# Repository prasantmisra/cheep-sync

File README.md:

CheepSync: A Time Synchronization Service for Resource Constrained Bluetooth LE Advertisers
--------------------------------------------------------------------------------------------

Bluetooth Low Enegy (BLE) is a subset of the Bluetooth v4:0 stack, and is designed for low-power applications interested in knowing the state of the physical world.
BLE has inherited several technical features from Classic Bluetooth that provide for robust, reliable connections. However, the most significant difference is its asymmetric design. While the standard
mode of operation is typically based on a master device connected to a number of slave devices, it offers a new feature in the form of an ‘advertisement’ (configurable through the broadcast/peripheral mode of BLE).
BLE provides a range of broadcast advertising modes, of which the most energy efficient is the non-connectable undirected advertising mode (ADV_NONCONN_IND): a transmit-only, broadcaster mode without any listen window.

CheepSync is an open source time synchronization service for BLE advertisers in ADV_NONCONN_IND mode.
Designed on top of the existing Bluetooth v4.0 standard, the CheepSync framework utilizes low-leveltimestamping and comprehensive error compensation mechanisms
for overcoming uncertainties in message transmission, clock drift and other system specific constraints. 

The current implementation of CheepSync is on custom designed nRF24Cheep beacon platforms (as broadcasters) and commercial off-the-shelf Android ported
smartphones (as passive listeners).

Configurations:
--------------------------------------------------------------------------------------------
Transmitter:

1. Go to URL http://www.kpitgnutools.com/index.php, and register. Upon successful registration, you will receive a username and password by email.
2. Using these credentials, download RL78 installer along with e2studio.
3. Import ? into the e2studio IDE.

Receiver:

1. Install the custom android ROM for the phone.

  We used KitKat on Nexus 5. There are two ways to do it:
  
  First:--------------
    Build the android phone according to the blog post (http://nosemaj.org/howto-build-android-kitkat-nexus-5)
    For incremental builds:
      source build/envsetup.sh
      lunch
      make updatepackage -j10
      make snod
      mmm /path/to/directory
      sudo chmod -R 755 
  
  Second:-------------
    Refer the cynogenmod website (http://www.cyanogenmod.org/)
  
2. Root the android phone
3. Install busybox installer for android
4. Start the transmitter
5. Run the android application
6. Observe the file /sdcard/log_after using adb shell and observing the contents.

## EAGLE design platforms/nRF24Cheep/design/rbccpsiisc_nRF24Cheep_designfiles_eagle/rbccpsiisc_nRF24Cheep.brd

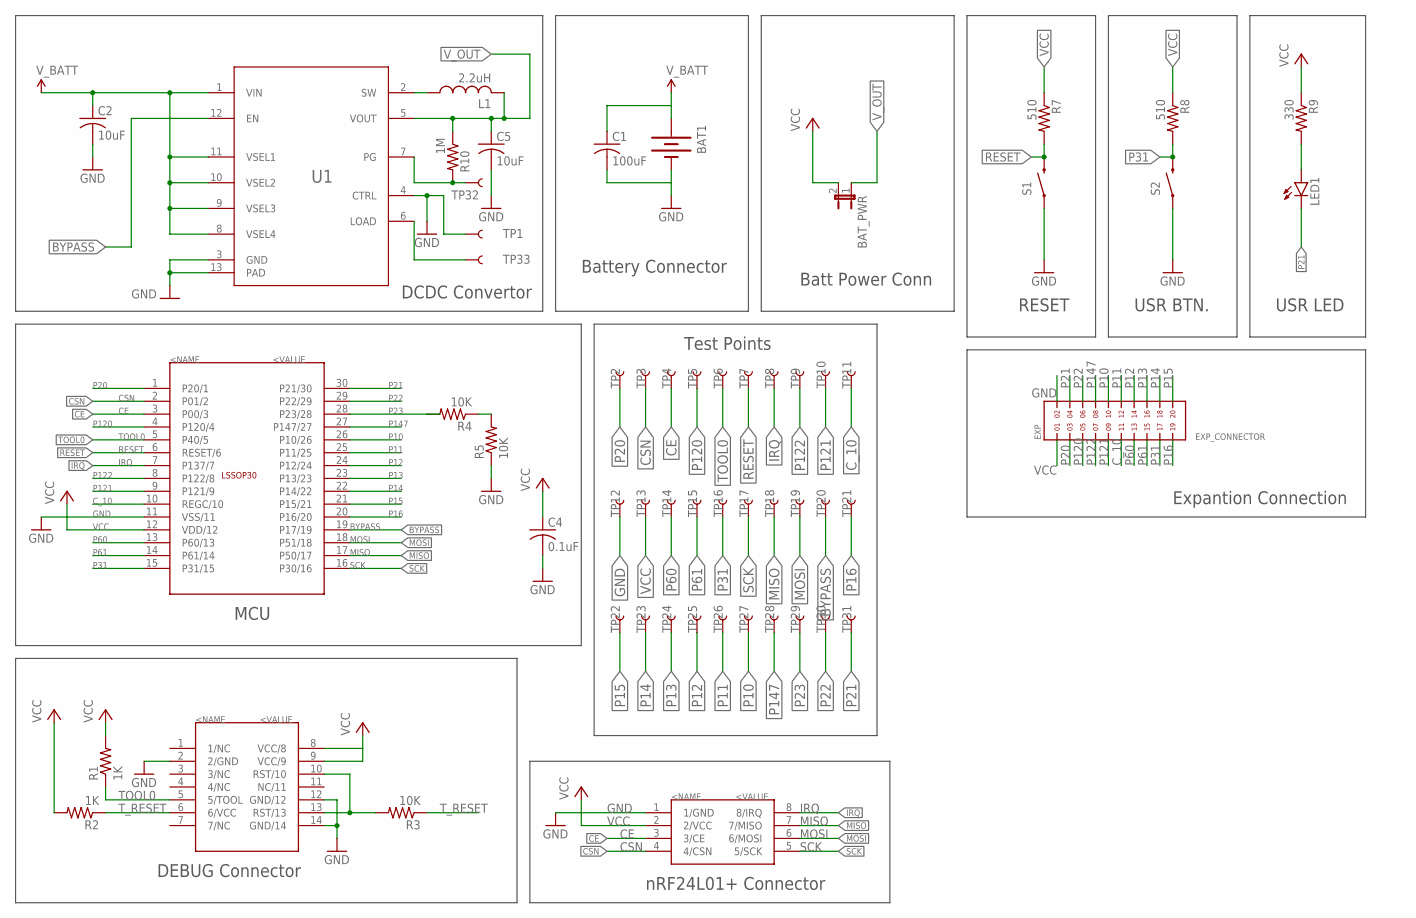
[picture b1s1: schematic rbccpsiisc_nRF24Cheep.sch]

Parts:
BAT1: BATTERY20SMD; BATTCON_20MM
BAT_PWR: JUMPER-2PTH; 1X02
C1: 100uF; C1206K
C2, C5: 10uF; C0603K
C4: 0.1uF; C0603K
EXP: EXP_CONNECTOR; 2X10
L1: 2.2uH; L2012C
LED1: LED0603; LED-0603
NRFSOCKET: BERG_NRF24_NRF24
R1, R2: 1K; R0603
R3, R4, R5: 10K; R0603
R7, R8: 510; R0603
R9: 330; R0603
R10: 1M; R0603
RENASENCE: SSOP30_SSOP30
S1, S2: SWITCH-MOMENTARY-2-SMD-1101NE; TACTILE-SWITCH-1101NE
TP1, TP2, TP3, TP4, TP5, TP6, TP7, TP8, TP9, TP10, TP11, TP12, TP13, TP14, TP15, TP16, TP17, TP18, TP19, TP20, TP21, TP22, TP23, TP24, TP25, TP26, TP27, TP28, TP29, TP30, TP31, TP32, TP33: TEST-POINT3X4; PAD.03X.04
U1: TPS62740DSST; DSS0012A
U$3: BERG_5_BERG_14; BERG_5_BERG_5

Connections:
CE: NRFSOCKET.3 (3/CE), RENASENCE.3 (P00/3), TP4.P$1
CSN: NRFSOCKET.4 (4/CSN), RENASENCE.2 (P01/2), TP3.P$1
C_10: EXP.11, RENASENCE.10 (REGC/10), TP11.P$1
GND: BAT1.2 (-), C1.2, C2.2, C4.2, C5.2, EXP.2, NRFSOCKET.1 (1/GND), R5.1, RENASENCE.11 (VSS/11), S1.P$1 (1), S2.P$1 (1), TP1.P$1, TP12.P$1, U1.3 (GND), U1.4 (CTRL), U1.13 (PAD), U$3.2 (2/GND), U$3.12 (GND/12), U$3.14 (GND/14); also elsewhere on the board
IRQ: NRFSOCKET.8 (8/IRQ), RENASENCE.7 (P137/7), TP8.P$1
MISO: NRFSOCKET.7 (7/MISO), RENASENCE.17 (P50/17), TP18.P$1
MOSI: NRFSOCKET.6 (6/MOSI), RENASENCE.18 (P51/18), TP19.P$1
unnamed: LED1.A, R9.2
unnamed: TP33.P$1, U1.6 (LOAD)
unnamed: L1.1, U1.2 (SW)
unnamed: R10.2, TP32.P$1, U1.7 (PG)
unnamed: R4.1, R5.2
P10: EXP.10, RENASENCE.26 (P10/26), TP27.P$1
P11: EXP.12, RENASENCE.25 (P11/25), TP26.P$1
P12: EXP.14, RENASENCE.24 (P12/24), TP25.P$1
P13: EXP.16, RENASENCE.23 (P13/23), TP24.P$1
P14: EXP.18, RENASENCE.22 (P14/22), TP23.P$1
P15: EXP.20, RENASENCE.21 (P15/21), TP22.P$1
P16: EXP.19, RENASENCE.20 (P16/20), TP21.P$1
P20: EXP.3, RENASENCE.1 (P20/1), TP2.P$1
P21: EXP.4, LED1.C, RENASENCE.30 (P21/30), TP31.P$1
P22: EXP.6, RENASENCE.29 (P22/29), TP30.P$1
P23: R4.2, RENASENCE.28 (P23/28), TP29.P$1
P31: EXP.17, R8.2, RENASENCE.15 (P31/15), S2.P$2 (2), TP16.P$1
P60: EXP.13, RENASENCE.13 (P60/13), TP14.P$1
P61: EXP.15, RENASENCE.14 (P61/14), TP15.P$1
P120: EXP.5, RENASENCE.4 (P120/4), TP5.P$1
P121: EXP.9, RENASENCE.9 (P121/9), TP10.P$1
P122: EXP.7, RENASENCE.8 (P122/8), TP9.P$1
P147: EXP.8, RENASENCE.27 (P147/27), TP28.P$1
RESET: R3.2, R7.2, RENASENCE.6 (RESET/6), S1.P$2 (2), TP7.P$1, U$3.10 (RST/10), U$3.13 (RST/13)
SCK: NRFSOCKET.5 (5/SCK), RENASENCE.16 (P30/16), TP17.P$1
TOOL0: R1.1, RENASENCE.5 (P40/5), TP6.P$1, U$3.5 (5/TOOL)
T_RESET: R2.1, R3.1, U$3.6 (6/VCC)
VCC: BAT_PWR.2, C4.1, EXP.1, NRFSOCKET.2 (2/VCC), R1.2, R2.2, R7.1, R8.1, R9.1, RENASENCE.12 (VDD/12), TP13.P$1, U$3.8 (VCC/8), U$3.9 (VCC/9)
V_OUT: BAT_PWR.1, C5.1, L1.2, R10.1, U1.5 (VOUT)

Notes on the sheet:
DCDC Convertor
MCU
DEBUG Connector
nRF24L01+ Connector
Battery Connector
Batt Power Conn
Expantion Connection
RESET
USR BTN.
USR LED
Test Points

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
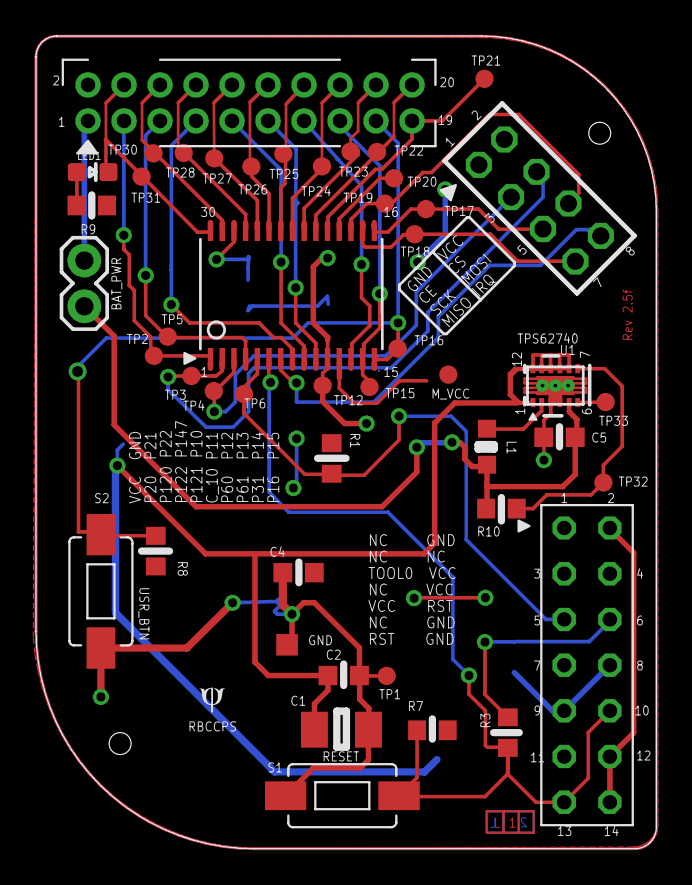
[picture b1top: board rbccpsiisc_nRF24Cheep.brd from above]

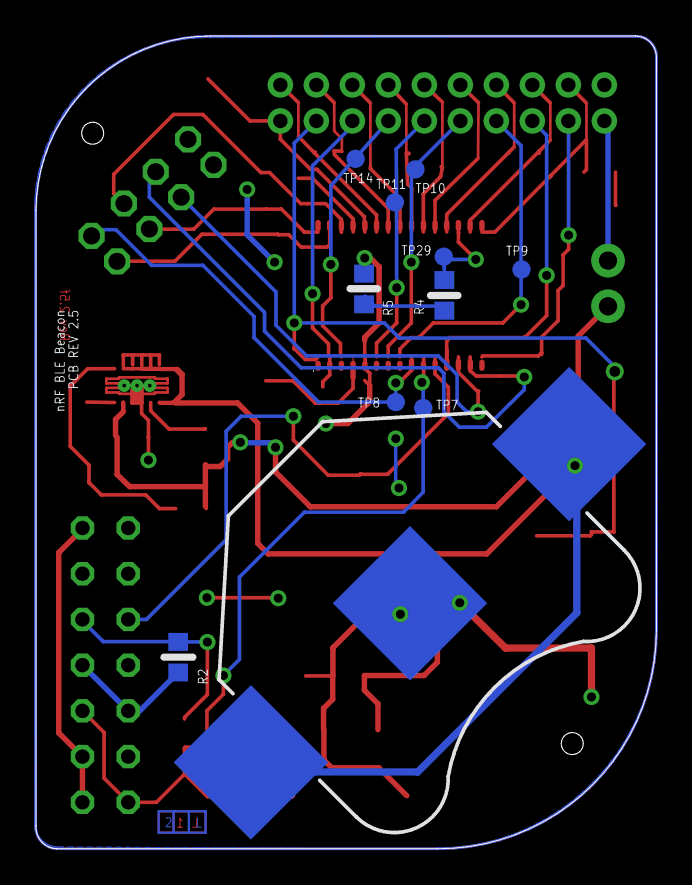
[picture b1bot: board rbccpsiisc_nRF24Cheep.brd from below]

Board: 2 copper layers, 34.5 x 45.2 mm, 58 parts (11 on the bottom side), 38 nets.

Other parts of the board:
GND: TPSQTP12SQ; TP12SQ

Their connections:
GND: GND.TP; also elsewhere on the board

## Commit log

2015-07-29 added folders
2015-07-30 updated license and added sstop and ssbot masks
2015-10-19 BOM added

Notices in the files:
platforms/nRF24Cheep/design/rbccpsiisc_nRF24Cheep_designfiles_eagle/rbccpsiisc_nRF24Cheep.brd:
Copyright (c) [2015] [Robert Bosch Centre for Cyber Physical Systems, Indian Institute of Science, Bangalore]
parts and their libraries:
SparkFun-Electromechanical: Licensing: Creative Commons ShareAlike 4.0 International - https://creativecommons.org/licenses/by-sa/4.0
